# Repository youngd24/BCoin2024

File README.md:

# BCoin2024
BurbSec Challenge Coin 2024

What's the challenge? Show up to a meetup! That's it, show up and new attendees get one.

## Why?

I've organized the South instance of BurbSec for coming up on a decace, I've always wanted something to be able to give new attendees as a sort of "thanks for coming". At the same time I wanted them to take something away, something to help them remember us, and to include the basic information about the Meetup itself, when, where and so on. While I was at it, why not have it be educational as well, in this case one of the most fundamentally basic of electronics circuits: the venerable 555 timer. I wanted it to be small, low cost, easy to modify for others, and dead simple to make. This version is 50mm in diameter and approximately 5mm thick, including the CR2016 battery, so it will fit in many (most) of the clear acrylic "challenge coin" or "collector coin" type cases. Double check on the thickness of whatever you find, that's where it gets to be sort of painful and expensive. A thinner, 40mm version is planned to help ease that challenge.

## How?

At the core is a basic astable 555 timer, programmed via the RC circuit to be around 4Hz, which in turn drives a decade counter to the perimeter LED's. It's a "chaser" sort of circuit, they light up in order, that's it, dead simple. It's driven from a single CR2016 battery, though the pads fit a CR2032 holder as well. The components on the board are good down to around 2.6V so the battery should hold up for a bit, how long though, who knows, this thing isn't meant to run all day, it's a token.

## Schematic

## Front

## Back

## Assembled

## Hacking it

If you want to adjust the rate at which the LED's flash around the edge you can swap out the R1/R2/C1 components that drive the 555 (astable) timer circuit. The value they're set to in the current form will drive them at 4.8 Hz, current values are:

R1 - 10k - 0603 size\
R2 - 10k - 0603 size\
C1 - 10uF - 0805 size

DigiKey has a great tool to calculate the values [here](https://www.digikey.com/en/resources/conversion-calculators/conversion-calculator-555-timer), just be sure to select the "astable" one. Order some options from them, break out the soldering iron and hack it up!

## Modifying it

Feel free to change whatever you'd like in the design, circuit or PCB. Make sure you run the ERC against the schematic as well as the DRC against the PCB, this will help catch any basic errors you may have introduced. Once you're ready use [these instructions](https://www.pcbway.com/blog/help_center/How_to_Generate_Gerber_and_Drill_Files_in_KiCad_7_0_ab0d12bb.html) to generate the Gerber and drill files needed for manufacturing.

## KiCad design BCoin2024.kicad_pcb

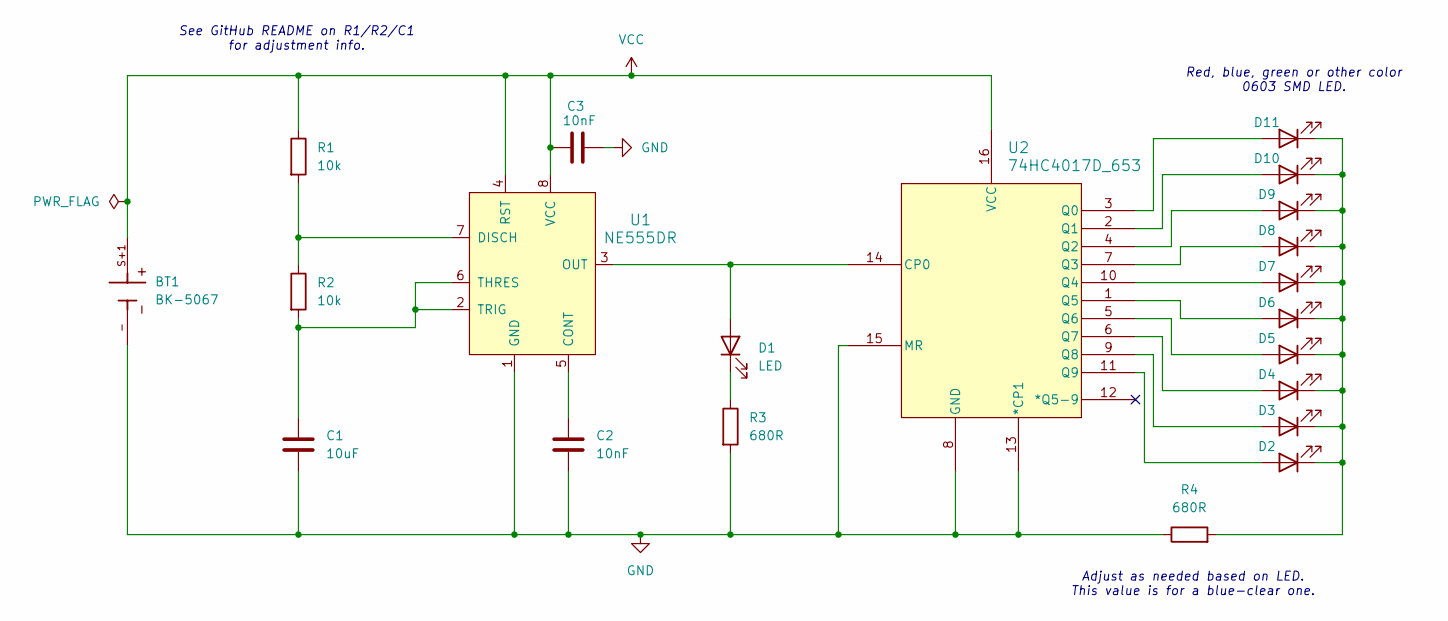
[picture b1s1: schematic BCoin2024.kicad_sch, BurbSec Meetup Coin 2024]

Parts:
BT1: BK-5067; BAT_BK-5067; PARTREV D
C1: 10uF; C_0805_2012Metric
C2, C3: 10nF; C_0603_1608Metric
D1, D2, D3, D4, D5, D6, D7, D8, D9, D10, D11: LED; LED_0603_1608Metric
R1, R2: 10k; R_0603_1608Metric
R3, R4: 680R; R_0603_1608Metric
U1: NE555DR; SOIC-8_W3.9mm; MPN NE555DR; Digi-Key_PN 296-6501-1-ND
U2: 74HC4017D_653; SO16_SOT109-1_NEX

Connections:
GND: BT1.-, C1.2, C2.2, C3.2, R3.2, R4.1, U1.1 (GND), U2.8 (GND), U2.13 (*CP1), U2.15 (MR)
unnamed: D1.2 (A), U1.3 (OUT), U2.14 (CP0)
unnamed: D1.1 (K), R3.1
unnamed: D2.2 (A), U2.11 (Q9)
unnamed: D3.2 (A), U2.9 (Q8)
unnamed: D4.2 (A), U2.6 (Q7)
unnamed: D5.2 (A), U2.5 (Q6)
unnamed: D6.2 (A), U2.1 (Q5)
unnamed: D7.2 (A), U2.10 (Q4)
unnamed: D8.2 (A), U2.7 (Q3)
unnamed: D9.2 (A), U2.4 (Q2)
unnamed: D10.2 (A), U2.2 (Q1)
unnamed: D2.1 (K), D3.1 (K), D4.1 (K), D5.1 (K), D6.1 (K), D7.1 (K), D8.1 (K), D9.1 (K), D10.1 (K), D11.1 (K), R4.2
unnamed: D11.2 (A), U2.3 (Q0)
unnamed: C2.1, U1.5 (CONT)
unnamed: R1.2, R2.1, U1.7 (DISCH)
unnamed: C1.1, R2.2, U1.2 (TRIG), U1.6 (THRES)
VCC: BT1.S+1, C3.1, R1.1, U1.4 (RST), U1.8 (VCC), U2.16 (VCC)

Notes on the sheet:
Adjust as needed based on LED. This value is for a blue-clear one.
Red, blue, green or other color 0603 SMD LED.
See GitHub README on R1/R2/C1 for adjustment info.

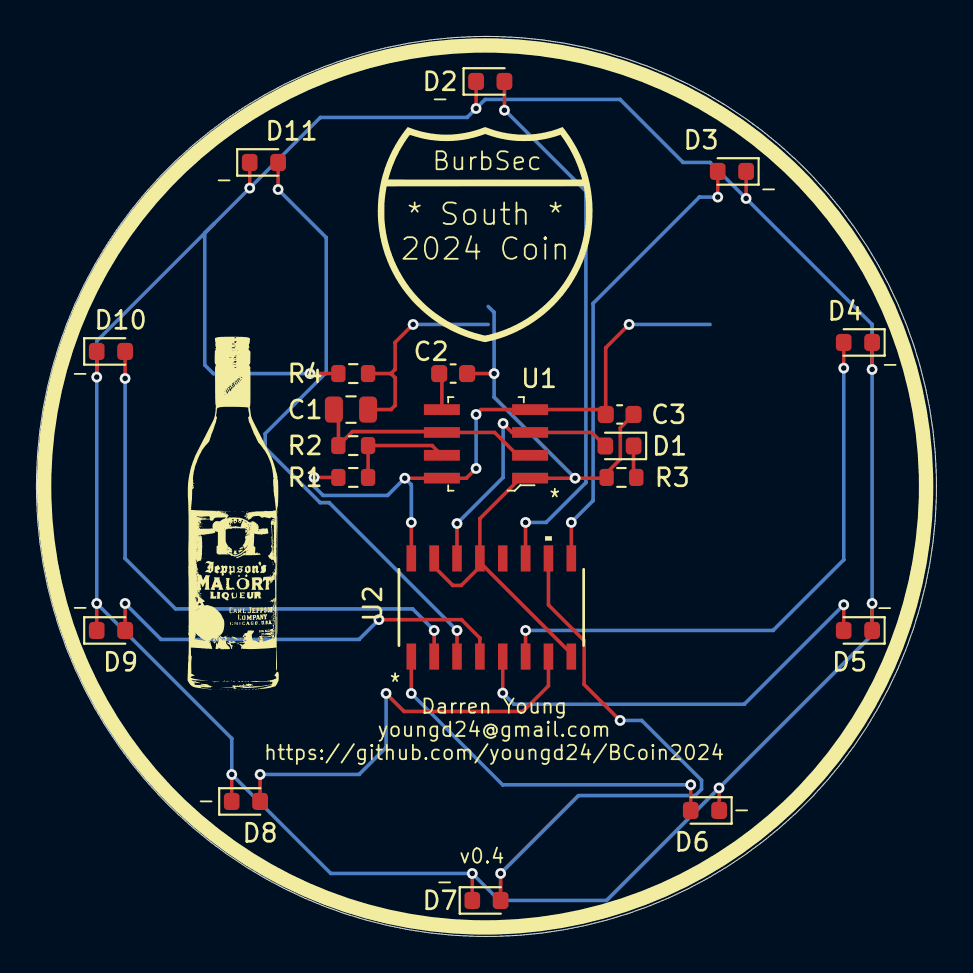
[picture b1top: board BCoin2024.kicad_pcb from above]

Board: 2 copper layers, 50.0 x 50.0 mm, 21 parts (1 on the bottom side), 18 nets.

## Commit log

2024-12-10 added ignore file
2024-12-10 initial add
2024-12-10 KiCAD cache update commit
2024-12-10 added datasheets
2024-12-10 added assets and images
2024-12-11 added 0.2 schematic
2024-12-12 Version 0.3
2024-12-12 added gerbers directory
2024-12-12 added v0.3 gerber files
2024-12-12 Update README.md
    Added text and image links.
2024-12-12 added schematic
2024-12-20 added malort footprint
2024-12-20 Adding v0.4 changes
2024-12-20 Generated v0.4 Gerber
2024-12-20 Updated images
2024-12-20 starting adding modification instructions
2024-12-20 added updated 0.4 schematic
2024-12-20 Update README.md
    Changed to 0.4 images.
2024-12-20 Added PCBWAY PN text to rear of board, generated new gerbers for it
2024-12-20 Update README.md
    Added more text to README
2024-12-20 added pcbway ignore and WayWayWay text for SN replacements
2024-12-27 added pic of completed coins
2025-01-06 added BOM
2025-01-06 minor update to bom
